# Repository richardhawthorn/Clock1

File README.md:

### Description

PCB and Arduino code for a basic clock

<div id="link">
	<a href="http://www.deluxecapacitor.com/projects/view/1">Project Page</a>
</div>

### Features

- 4 character 7-segment LED display
- ATMEGA328P with Arduino boot-loader
- 5V operation @ 16Mhz
- DS3231 battery backed clock
- 2x buttons to update minutes and seconds
- Mini USB power connector
- FTDI programming port
- ICSP port

#### Changes

Clock1.1 - First version
Clock1.2 - Replaced surface mount USB connector with through hole version

### License

This work is licensed under a Creative Commons Attribution-ShareAlike 4.0 International License.

<br />
Designed by <a xmlns:cc="http://creativecommons.org/ns#" href="http://www.richardhawthorn.com" property="cc:attributionName" rel="cc:attributionURL" target="_blank">Richard Hawthorn</a><br />
<a rel="license" href="http://creativecommons.org/licenses/by-sa/4.0/" target="_blank">View License</a>

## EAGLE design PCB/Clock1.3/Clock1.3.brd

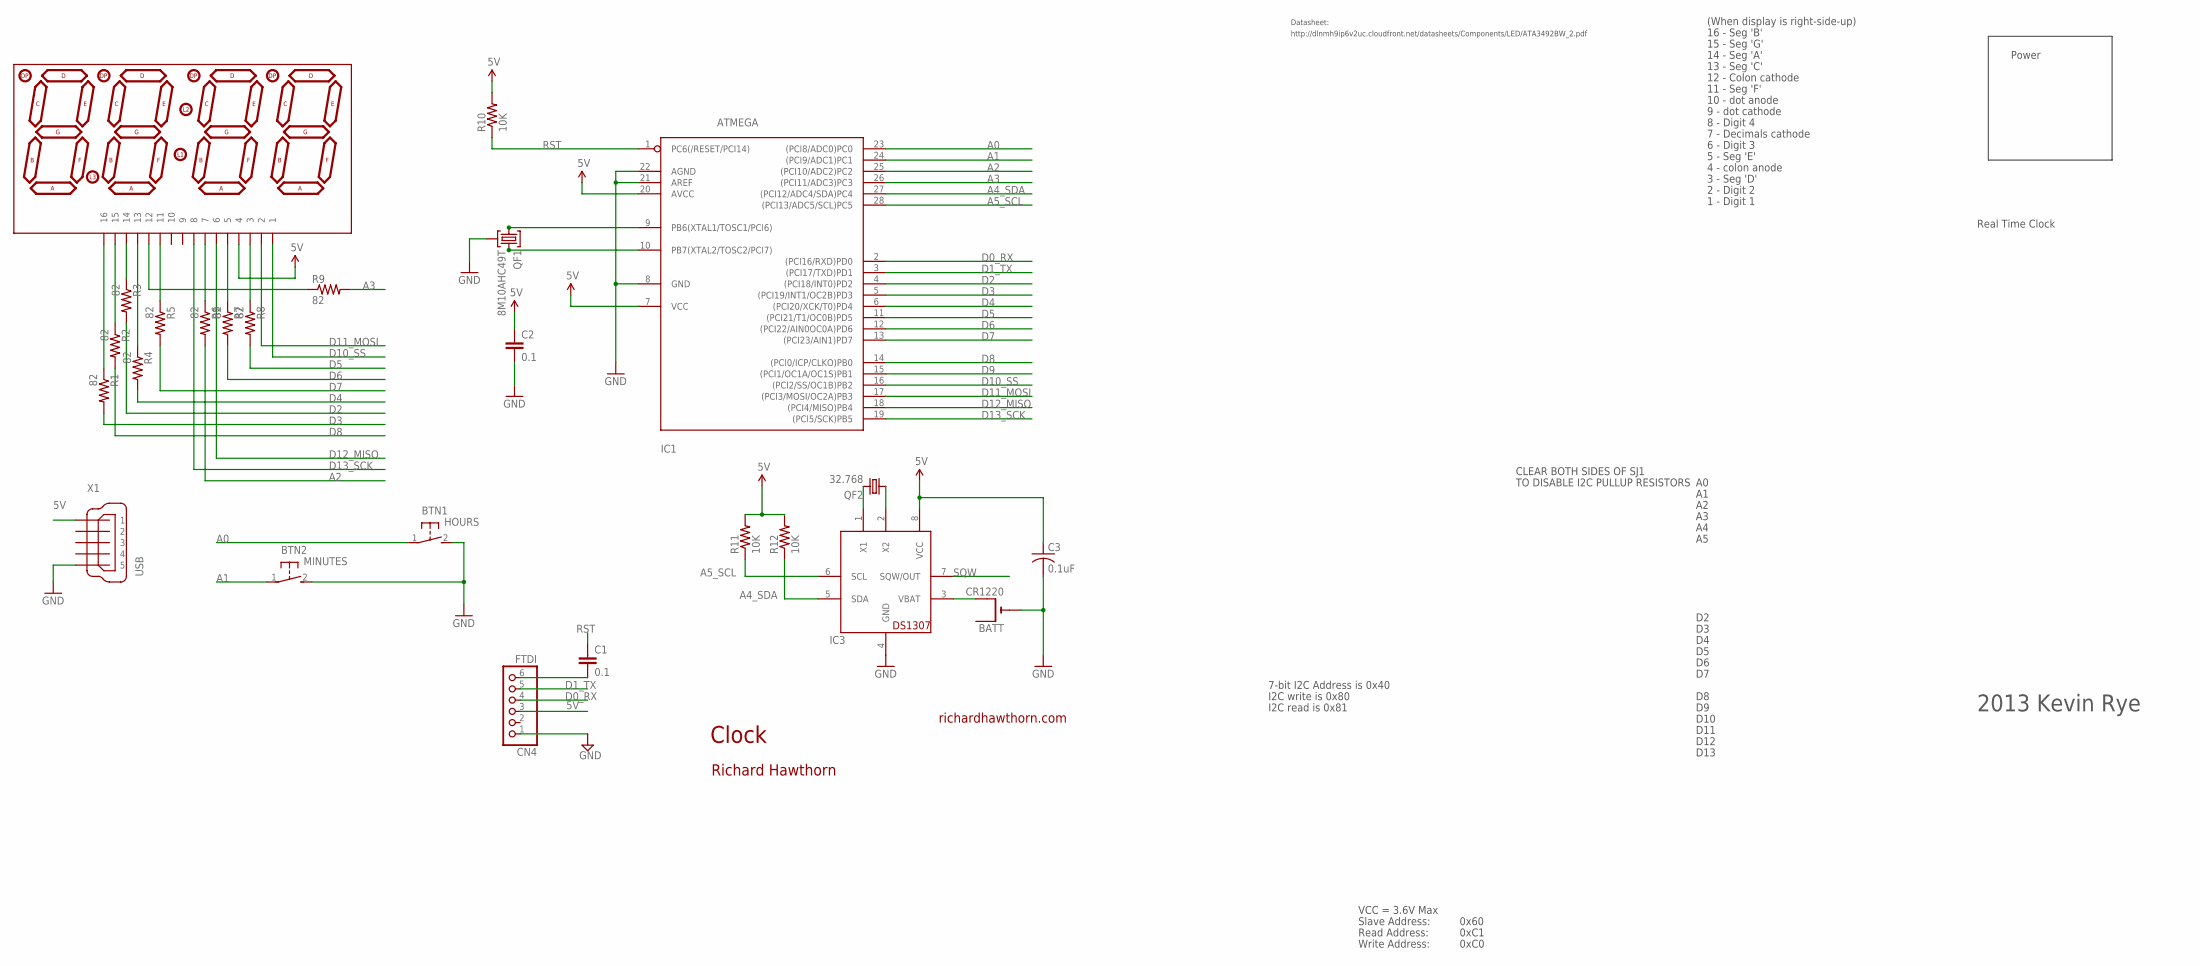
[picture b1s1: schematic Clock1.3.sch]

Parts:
BATT: CR1220; CR1220-SMD
BTN1: HOURS; DTS-3
BTN2: MINUTES; DTS-3
C1, C2: 0.1; CAP-PTH-SMALL2
C3: 0.1uF; C025-025X050
CN4: FTDI; 1X06
IC1: ATMEGA; DIL28-3-ROUND
IC3: DS1307; DIL08
LED1: 7SEG-4DIGIT; SPARKFUN_7-SEGMENT-4DIGIT
QF1: 8M10AHC49T; HC49U
QF2: 32.768; TC38H
R1, R2, R3, R4, R5, R6, R7, R8, R9: 82; 0204/7
R10, R11, R12: 10K; 0204/7
X1: USB; 32005-601

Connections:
5V: C2.1, C3.1, CN4.3, IC1.7 (VCC), IC1.20 (AVCC), IC3.8 (VCC), LED1.4, R10.2, R11.2, R12.2, X1.1
A0: BTN1.1, IC1.23 ((PCI8/ADC0)PC0)
A1: BTN2.1, IC1.24 ((PCI9/ADC1)PC1)
A2: IC1.25 ((PCI10/ADC2)PC2), R6.2
A3: IC1.26 ((PCI11/ADC3)PC3), R9.2
A4_SDA: IC1.27 ((PCI12/ADC4/SDA)PC4), IC3.5 (SDA), R12.1
A5_SCL: IC1.28 ((PCI13/ADC5/SCL)PC5), IC3.6 (SCL), R11.1
D0_RX: CN4.4, IC1.2 ((PCI16/RXD)PD0)
D1_TX: CN4.5, IC1.3 ((PCI17/TXD)PD1)
D2: IC1.4 ((PCI18/INT0)PD2), R3.2
D3: IC1.5 ((PCI19/INT1/OC2B)PD3), R1.2
D4: IC1.6 ((PCI20/XCK/T0)PD4), R4.2
D5: IC1.11 ((PCI21/T1/OC0B)PD5), R8.2
D6: IC1.12 ((PCI22/AIN0OC0A)PD6), R7.2
D7: IC1.13 ((PCI23/AIN1)PD7), R5.2
D8: IC1.14 ((PCI0/ICP/CLKO)PB0), R2.2
D9: IC1.15 ((PCI1/OC1A/OC1S)PB1)
D10_SS: IC1.16 ((PCI2/SS/OC1B)PB2), LED1.1
D11_MOSI: IC1.17 ((PCI3/MOSI/OC2A)PB3), LED1.2
D12_MISO: IC1.18 ((PCI4/MISO)PB4), LED1.6
D13_SCK: IC1.19 ((PCI5/SCK)PB5), LED1.8
GND: BATT.-, BTN1.2, BTN2.2, C2.2, C3.2, CN4.1, IC1.8 (GND), IC1.21 (AREF), IC1.22 (AGND), IC3.4 (GND), QF1.2, X1.5
unnamed: BATT.+$2 (+1), IC3.3 (VBAT)
unnamed: LED1.16, R1.1
unnamed: LED1.15, R2.1
unnamed: LED1.12, R9.1
unnamed: LED1.7, R6.1
unnamed: IC3.1 (X1), QF2.2
unnamed: IC3.2 (X2), QF2.1
unnamed: IC1.9 (PB6(XTAL1/TOSC1/PCI6)), QF1.1
unnamed: C1.2, CN4.6
unnamed: LED1.13, R4.1
unnamed: LED1.14, R3.1
unnamed: LED1.11, R5.1
unnamed: IC1.10 (PB7(XTAL2/TOSC2/PCI7)), QF1.3
unnamed: LED1.5, R7.1
unnamed: LED1.3, R8.1
RST: C1.1, IC1.1 (PC6(/RESET/PCI14)), R10.1
SQW: IC3.7 (SQW/OUT)

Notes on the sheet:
Clock
richardhawthorn.com
Richard Hawthorn
CLEAR BOTH SIDES OF SJ1
TO DISABLE I2C PULLUP RESISTORS
7-bit I2C Address is 0x40
I2C write is 0x80
I2C read is 0x81
VCC = 3.6V Max
Read Address:
Write Address:
Slave Address:
0x60
0xC1
0xC0
14 - Seg 'A'
13 - Seg 'C'
12 - Colon cathode
11 - Seg 'F'
10 - dot anode
9 - dot cathode
8 - Digit 4
7 - Decimals cathode
6 - Digit 3
5 - Seg 'E'
4 - colon anode
3 - Seg 'D'
2 - Digit 2
Real Time Clock
1 - Digit 1
15 - Seg 'G'
16 - Seg 'B'
D10
D11
D12
D13
http://dlnmh9ip6v2uc.cloudfront.net/datasheets/Components/LED/ATA3492BW_2.pdf
Datasheet:
Power
(When display is right-side-up)

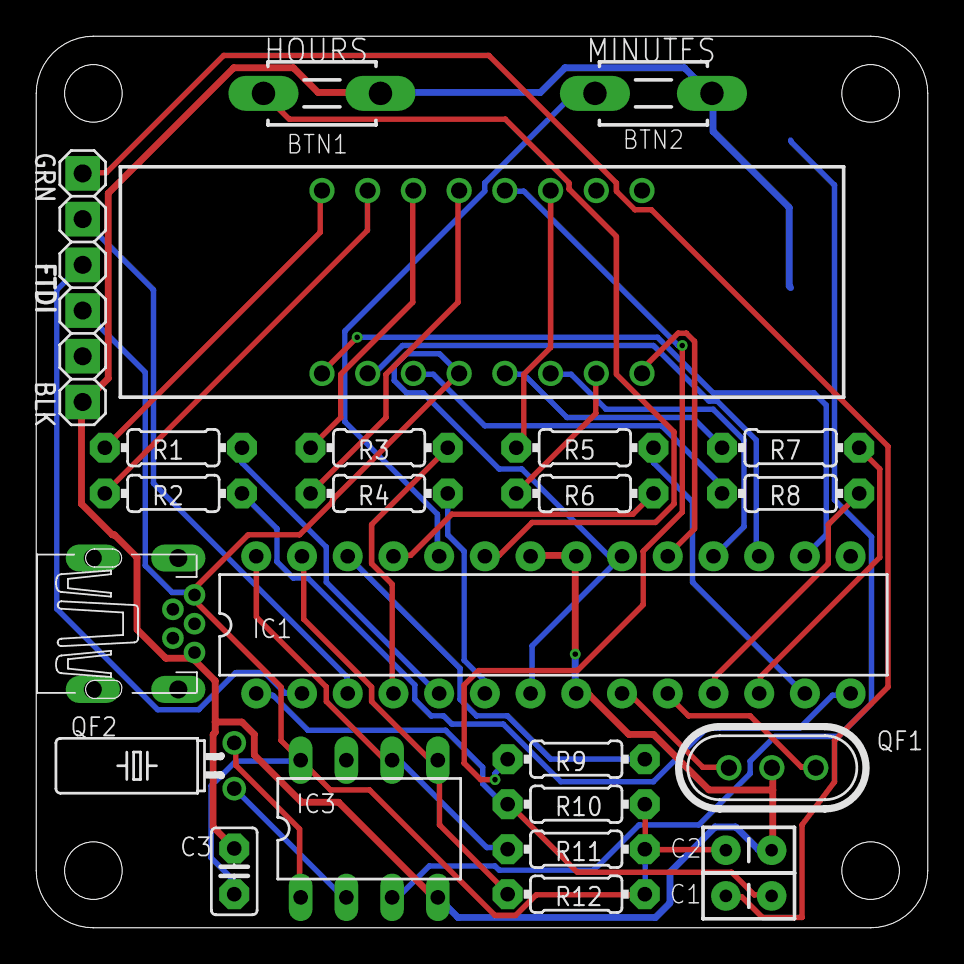
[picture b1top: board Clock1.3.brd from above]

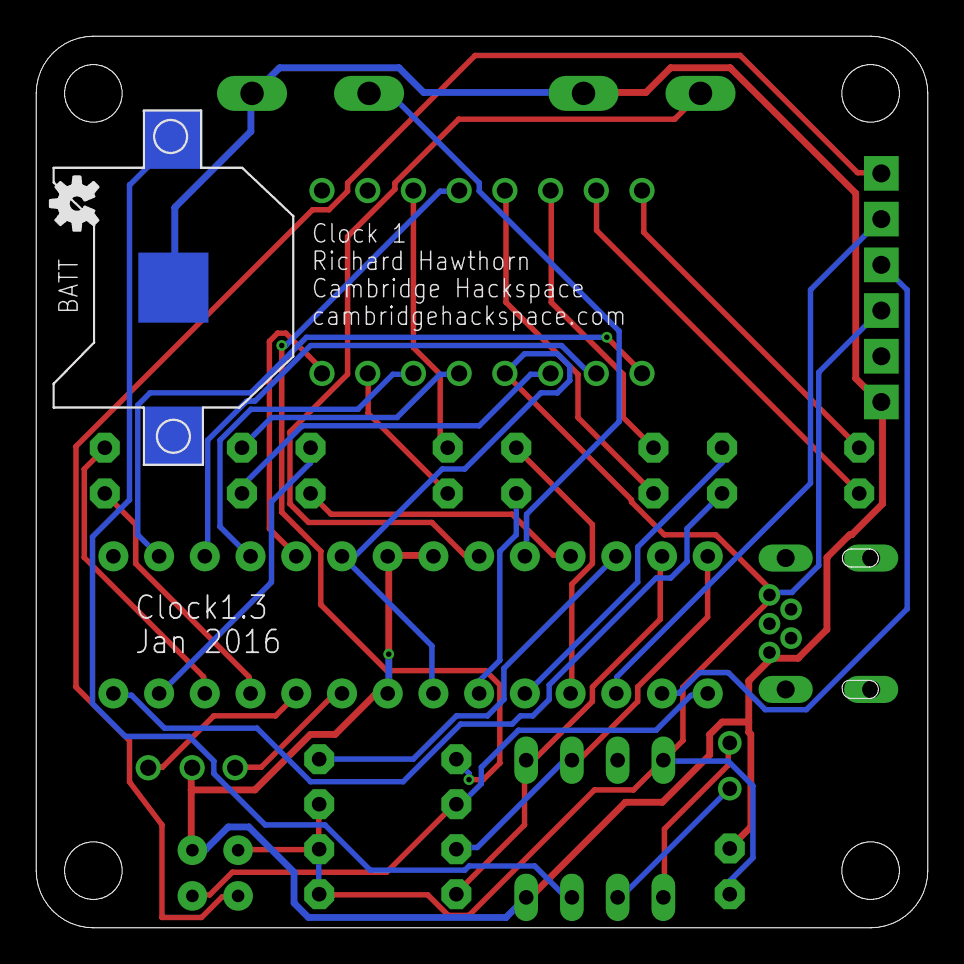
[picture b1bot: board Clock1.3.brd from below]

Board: 2 copper layers, 49.5 x 49.5 mm, 26 parts (2 on the bottom side), 37 nets.

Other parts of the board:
U$3: OSHW-LOGO-S

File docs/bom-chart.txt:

### Part list

| Qty | Value       | Device         | Parts                             |
| --- | ----------- | -------------- | --------------------------------- |
| 3   |  0.1uf      | Capacitor      | C1, C2, C3                        |
| 4   |  10K        | Resistor       | R10, R11, R12, R13                |
| 1   |  680r       | Resistor       | R9                                |
| 8   |  82r        | Resistor       | R1, R2, R3, R4, R5, R6, R7, R8    |
| 1   |  7SEG       | 7 Segment LED  | LED1                              |
| 1   |  8M10AHC49T | Crystal        | QF1                               |
| 1   |  ATMAGE328P | Processor      | IC1                               |
| 1   |  CR1220     | Battery        | BATT                              |
| 1   |  DS3231     | Calendar       | IC2                               |
| 1   |  FTDI       | Connector-1X6  | CN4                               |
| 1   |  ICSP       | Connector-2X3  | ICSP1   (No component needed)     |
| 1   |  HOURS      | Button         | BTN1                              |
| 1   |  MINUTES    | Button         | BTN2                              |
| 1   |  USB        | Mini USB       | CN1                               |

### Additional Hardware

| Qty | Part         | 
| --- | ------------ |
| 1   | Battery      |
| 1   | IC Socket    | 
| 1   | PCB          |
| 1   | Front Plate  |
| 4   | Pillars      |
| 8   | Screws       |

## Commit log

2014-12-05 Added pcb
2015-06-07 added Arduino code
2015-06-07 add pcb images
2015-06-07 add readme
2015-06-07 updated images
2015-06-20 Add images and update readme
2015-07-11 added instructions and bom
2015-07-12 added parts photos
2015-07-14 update bom
2015-07-14 update instructions
2015-07-14 updated instructions
2015-07-15 update to Arduino code
2015-11-05 added images
2015-11-05 added gerbers for clock1.2
2016-01-10 initial design for v1.3
2016-04-16 add support for clock2
2016-11-08 small adjustment to the code
2016-11-08 update to schematic
2016-11-08 updated readme and added bom

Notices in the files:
parts and their libraries:
SparkFun-Aesthetics: Licensing: CC v3.0 Share-Alike You are welcome to use this library for commercial purposes.
